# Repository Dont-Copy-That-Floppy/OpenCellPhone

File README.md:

# OpenCellPhone

**An open hardware + software cell phone using the global GSM network.**

Arduino-based and fully open-source, OpenCellPhone is a DIY mobile phone project that runs on AT commands, handles SMS/calls, and supports a touch-based interface with a custom-built GUI.

[2014/15 Hackaday Quarterfinalist](https://hackaday.io/project/2478-open-source-cell-phone)

---

## 🚀 Features

- Full support for **SMS send/receive**
- **Touch-based dial pad** and passcode lock screen
- **Call handling** (dial, receive, hang up)
- Basic **notifications**, **call timer**, and **incoming caller display**
- Real-time **clock display** from GSM module (`AT+CCLK`)
- Visual **signal strength** display (`AT+CSQ`)
- **Low-power display handling** with timeout/dim/sleep modes

---

## 🧠 Planned and Future Features

### Needed Features

- Lookup table for pixel width for screen formatting
- Sent SMS display and storage
- Secondary storage for messages
- Emergency calling from passcode screen
- In-call volume adjustment
- Call waiting support (`AT+CHLD`)
- Missed call tracking
- SMS management (delete, reorder, store)
- Signal strength meter
- Re-dial last number (`ATDL`)
- Notification screen with better intelligence

### Future Features

- Bluetooth & FM Radio
- Contact List / Phone Book
- Adjustable screen brightness
- Airplane mode (`AT+CFUN`)
- SMS sorting by sender/contact
- Swipe gestures for UI
- MMS view/send, image handling
- Light sensor and auto-brightness
- MP3/audio playback
- GPS & accelerometer
- Display output
- Web browser
- Ringtones
- Configurable settings via touch UI

---

## 📋 SIM Limitations

- SIM card storage is limited to **30 SMS messages**

---

## ⚙️ Build Info

### Architecture

- Built with **Arduino IDE**
- Written in C/C++ with **low-level serial AT command** integration
- GUI rendered using **RA8875 touchscreen driver**
- Touchscreen and backlight managed through **PWM and pin control**

### Libraries & Tools

- `RA8875` display/touch driver
- Standard `Serial`, `Wire`, and `SPI` Arduino libs
- Custom utility functions for character buffering and cursor logic

---

## 🧪 AT Command References

| Command                                   | Description                |
|-------------------------------------------|----------------------------|
| `ATD*99#`                                 | Dial Access Point          |
| `AT+CGDCONT=1,"IP","access.point.name"`   | Defines PDP context        |
| `AT+VRX`                                  | Record in-call audio       |
| `AT+COPS=?`                               | List available networks     |
| `AT+CSQ`                                  | Check signal strength      |
| `ATDL`                                    | Redial last number         |
| `AT+CHLD`                                 | Call waiting options       |

---

## 🧰 Development Setup

### Folder Structure

```text
/PrototypePhone
│
├── /lib                # Optional custom libraries
├── PrototypePhone.ino  # main file

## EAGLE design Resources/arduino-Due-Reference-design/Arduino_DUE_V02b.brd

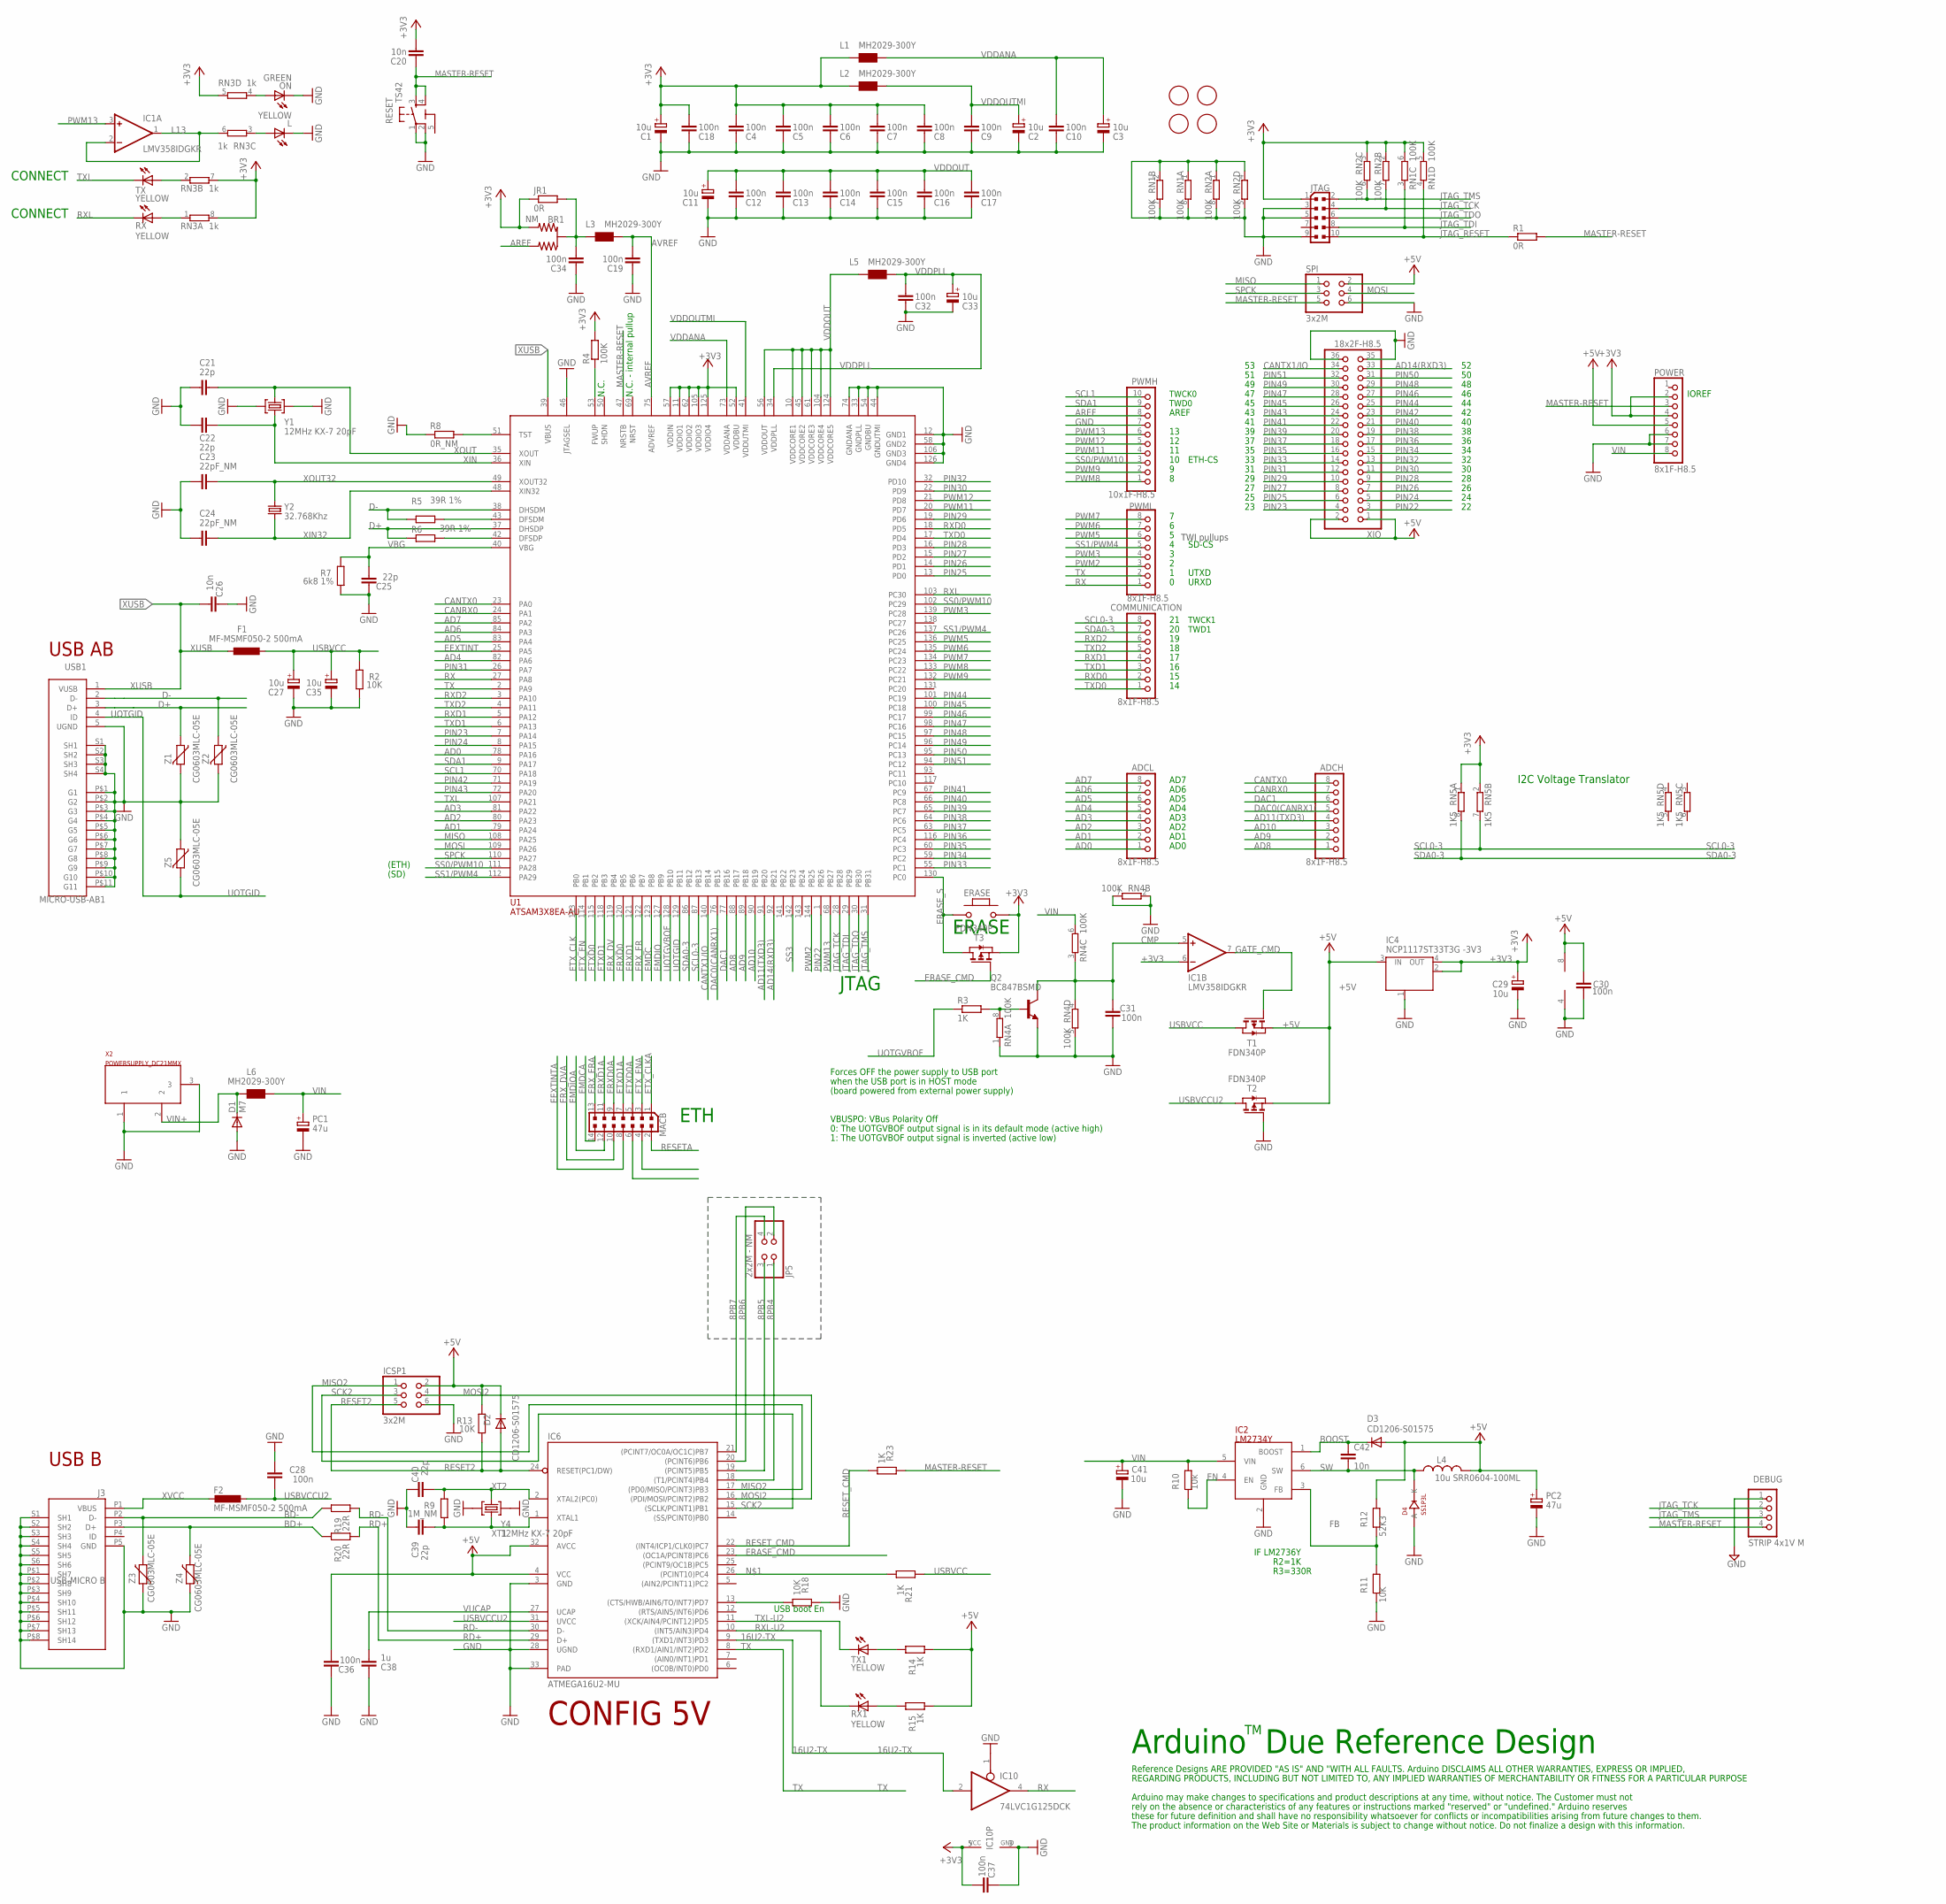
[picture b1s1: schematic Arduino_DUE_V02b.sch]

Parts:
ADCH: 8x1F-H8.5; 1X08
ADCL: 8x1F-H8.5; 1X08
BR1: NM; J0402
C1, C2, C3, C11, C27, C29, C33, C35, C41: 10u; SMC_B
C4, C5, C6, C7, C8, C9, C10, C12, C13, C14, C15, C16, C17, C18, C19, C28, C30, C31, C32, C34, C36, C37: 100n; C0402
C20, C26: 10n; C0402
C21, C22, C25, C39, C40: 22p; C0402
C23, C24: 22pF_NM; C0402
C38: 1u; C0402
C42: 10n; C0603-ROUND
COMMUNICATION: 8x1F-H8.5; 1X08
D1: M7; SMB
D2, D3: CD1206-S01575; MINIMELF
D4: SS1P3L; DO220AAL
DEBUG: STRIP 4x1V M; 1X04
ERASE: MYSMD_PB157; SMD_157SW
F1, F2: MF-MSMF050-2 500mA; L1812
FID1, FID2, FID3, FID4: FIDUCIALMOUNT; FIDUCIA-MOUNT
IC1: LMV358IDGKR; MSOP08
IC2: LM2734Y; SOT23-6
IC4: NCP1117ST33T3G -3V3; SOT223
IC6: ATMEGA16U2-MU; MLF32
IC10: 74LVC1G125DCK; SC70-5
ICSP1: 3x2M; 2X03
J3: USB-MICRO B; CON2_USB_MICRO_B_AT
JP5: 2x2M - NM; 2X02
JR1: 0R; R0402
JTAG: PINHEAD_PINHD-2X5PASSO127; PINHEAD_2X05_127
L: YELLOW; CHIP-LED0805
L1, L2, L3, L5, L6: MH2029-300Y; 0805
L4: 10u SRR0604-100ML; SRR0604
MACB: PINHEAD_PINHD-2X7PASSO127; PINHEAD_2X07_127
ON: GREEN; CHIP-LED0805
PC1, PC2: 47u; PANASONIC_D
POWER: 8x1F-H8.5; 1X08
PWMH: 10x1F-H8.5; 1X10
PWML: 8x1F-H8.5; 1X08
Q2: BC847BSMD; SOT23
R1: 0R; R0402
R2, R13, R18: 10K; R0402
R3, R14, R15, R21, R23: 1K; R0402
R4: 100K; R0402
R5, R6: 39R 1%; R0402
R7: 6k8 1%; R0603-ROUND
R8: 0R_NM; R0402
R9: 1M_NM; R0402
R10: 10k; R0402
R11: 10K; R0603-ROUND
R12: 52K3; R0603-ROUND
R19, R20: 22R; R0402
RESET: TS42
RN1, RN2, RN4: 100K; CAT16
RN3: 1k; CAY16
RN5: 1K5; CAT16
RX, RX1: YELLOW; CHIP-LED0805
SPI: 3x2M; 2X03
T1, T2, T3: FDN340P; SOT-23
TX, TX1: YELLOW; CHIP-LED0805
U1: ATSAM3X8EA-AU; LQFP144
USB1: MICRO-USB-AB1; MCR-AB1-S-RA-SMT
X2: POWERSUPPLY_DC21MMX; POWERSUPPLY_DC-21MM
XIO: 18x2F-H8.5; 2X18
Y1, Y4: 12MHz KX-7 20pF; CRYSTAL-3.2-2.5
Y2: 32.768Khz; RESONATOR_EPSON_FC_145
Z1, Z2, Z3, Z4, Z5: CG0603MLC-05E; CT/CN0603

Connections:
5-GND: RESET.5 (5-GND)
8PB4: IC6.18 ((T1/PCINT4)PB4), JP5.1
8PB5: IC6.19 ((PCINT5)PB5), JP5.3
8PB6: IC6.20 ((PCINT6)PB6), JP5.2
8PB7: IC6.21 ((PCINT7/OC0A/OC1C)PB7), JP5.4
16U2-TX: IC6.9 ((TXD1/INT3)PD3), IC10.2 (I)
+3V3: BR1.3 (2), C1.+, C4.2, C5.2, C6.2, C7.2, C8.2, C18.2, C20.2, C29.+, C37.1, ERASE.1, IC1.6 (-IN), IC4.2 (OUT), IC4.4 (OUT), IC10.5 (VCC), JR1.1, JTAG.1, L1.1, L2.1, POWER.2, POWER.4, R4.2, RN1.5 (2), RN1.6 (2), RN2.2 (1), RN2.3 (1), RN3.5 (2), RN3.7 (2), RN3.8 (2), RN5.1, RN5.2 (1), T3.2 (S), U1.11 (VDDIO1), U1.52 (VDDBU), U1.57 (VDDIN), U1.62 (VDDIO2), U1.105 (VDDIO3), U1.125 (VDDIO4)
+5V: C30.2, C36.1, D2.C, D3.A, IC1.8 (V+), IC4.3 (IN), IC6.4 (VCC), IC6.32 (AVCC), ICSP1.2, L4.P$2 (2), PC2.+, POWER.5, R12.1, R13.2, R14.1, R15.1, SPI.2, T1.2 (S), T2.2 (S), XIO.1, XIO.2
AD0: ADCL.1, U1.78 (PA16)
AD1: ADCL.2, U1.79 (PA24)
AD2: ADCL.3, U1.80 (PA23)
AD3: ADCL.4, U1.81 (PA22)
AD4: ADCL.5, U1.82 (PA6)
AD5: ADCL.6, U1.83 (PA4)
AD6: ADCL.7, U1.84 (PA3)
AD7: ADCL.8, U1.85 (PA2)
AD8: ADCH.1, U1.88 (PB17)
AD9: ADCH.2, U1.89 (PB18)
AD10: ADCH.3, U1.90 (PB19)
AD11(TXD3): ADCH.4, U1.91 (PB20)
AD14(RXD3): U1.92 (PB21), XIO.33
AREF: BR1.1, PWMH.8
AVREF: C19.2, L3.2, U1.75 (ADVREF)
AVREFL: BR1.2 (C), C34.2, JR1.2, L3.1
BD+: J3.P3 (D+), R20.2, Z4.2
BD-: J3.P2 (D-), R19.2, Z3.2
BOOST: C42.1, D3.C, IC2.1 (BOOST)
CANRX0: ADCH.7, U1.24 (PA1)
CANTX0: ADCH.8, U1.23 (PA0)
CANTX1/IO: U1.140 (PB14), XIO.34
CMP: C31.2, IC1.5 (+IN), Q2.3 (C), RN4.3 (1), RN4.4 (1)
D+: R6.1, U1.37 (DHSDP), USB1.3 (D+), Z1.1
D-: R5.1, U1.38 (DHSDM), USB1.2 (D-), Z2.1
DAC0(CANRX1): ADCH.5, U1.76 (PB15)
DAC1: ADCH.6, U1.77 (PB16)
DTR: IC6.13 ((CTS/HWB/AIN6/TO/INT7)PD7), R18.1
EEXTINT: U1.25 (PA5)
EEXTINTA: MACB.8
EMDC: U1.123 (PB8)
EMDCA: MACB.14
EMDIO: U1.127 (PB9)
EMDIOA: MACB.12 (13)
EN: IC2.4 (EN), R10.2
ERASE_CMD: IC6.23 ((OC1A/PCINT8)PC6), T3.3 (G)
ERASE_S: ERASE.2, T3.1 (D), U1.130 (PC0)
ERXD0: U1.120 (PB5)
ERXD0A: MACB.9
ERXD1: U1.121 (PB6)
ERXD1A: MACB.11
ERX_DV: U1.119 (PB4)
ERX_DVA: MACB.10
ERX_ER: U1.122 (PB7)
ERX_ERA: MACB.13 (12)
ETXD0: U1.115 (PB2)
ETXD0A: MACB.5
ETXD1: U1.118 (PB3)
ETXD1A: MACB.7
ETX_CLK: U1.113 (PB0)
ETX_CLKA: MACB.1
ETX_EN: U1.114 (PB1)
ETX_ENA: MACB.3
FB: IC2.3 (FB), R11.1, R12.2
GATE_CMD: IC1.7 (OUT), T1.3 (G)
GND: C1.-, C2.-, C3.-, C4.1, C5.1, C6.1, C7.1, C8.1, C9.1, C10.1, C11.-, C12.1, C13.1, C14.1, C15.1, C16.1, C17.1, C18.1, C19.1, C21.2, C22.2, C23.2, C24.2, C25.2, C26.2, C27.-, C28.2, C29.-, C30.1, C31.1, C32.1, C33.-, C34.1, C35.-, C36.2, C37.2, C38.2, C39.2, C40.2, C41.-, D1.A, D4.P$2 (A), DEBUG.1, IC1.4 (V-), IC2.2 (GND), IC4.1 (GND/ADJ), IC6.3 (GND), IC6.28 (UGND), IC6.33 (PAD), IC10.1 (OE), IC10.3 (GND), ICSP1.6, J3.P5 (GND), J3.P$1 (SH7), J3.P$2 (SH8), J3.P$3 (SH9), J3.P$4 (SH10), J3.P$5 (SH11), J3.P$6 (SH12), J3.P$7 (SH13), J3.P$8 (SH14), J3.S1 (SH1), J3.S2 (SH2), J3.S3 (SH3), J3.S4 (SH4), J3.S5 (SH5), J3.S6 (SH6), JTAG.3, JTAG.5, JTAG.9, L.C, ON.C, PC1.-, PC2.-, POWER.6, POWER.7, PWMH.7, Q2.2 (E), R2.1, R7.1, R8.1, R11.2, R18.2, RESET.1, RESET.2, RN1.1, RN1.2 (1), RN1.7 (2), RN1.8 (2), RN2.1, RN2.4 (1), RN2.5 (2), RN2.8 (2), RN4.1, RN4.2 (1), RN4.5 (2), RN4.7 (2), SPI.6, T2.3 (G), U1.12 (GND1), U1.33 (GNDPLL), U1.44 (GNDUTMI), U1.46 (JTAGSEL), U1.54 (GNDBU), U1.58 (GND2), U1.74 (GNDANA), U1.106 (GND3), U1.126 (GND4), USB1.5 (UGND), USB1.P$1 (G1), USB1.P$2 (G2), USB1.P$3 (G3), USB1.P$4 (G4), USB1.P$5 (G5), USB1.P$6 (G6), USB1.P$7 (G7), USB1.P$8 (G8), USB1.P$9 (G9), USB1.P$10 (G10), USB1.P$11 (G11), USB1.S1 (SH1), USB1.S2 (SH2), USB1.S3 (SH3), USB1.S4 (SH4), X2.1, X2.3, XIO.35, XIO.36, Y1.2 (GND), Y1.4 (GND), Y4.2 (GND), Y4.4 (GND), Z1.2, Z2.2, Z3.1, Z4.1, Z5.1
JTAG_RESET: JTAG.10, R1.1, RN1.4 (1)
JTAG_TCK: DEBUG.2, JTAG.4, RN2.7 (2), U1.28 (PB28)
JTAG_TDI: JTAG.8, RN1.3 (1), U1.29 (PB29)
JTAG_TDO: JTAG.6, U1.30 (PB30)
JTAG_TMS: DEBUG.3, JTAG.2, RN2.6 (2), U1.31 (PB31)
L13: IC1.1 (OUT), IC1.2 (-IN), RN3.6 (2)
MASTER-RESET: C20.1, DEBUG.4, POWER.3, R1.2, R23.2, RESET.3, RESET.4, SPI.5, U1.47 (NRSTB)
MISO: SPI.1, U1.108 (PA25)
MISO2: IC6.17 ((PD0/MISO/PCINT3)PB3), ICSP1.1
MOSI: SPI.4, U1.109 (PA26)
MOSI2: IC6.16 ((PDI/MOSI/PCINT2)PB2), ICSP1.4
unnamed: IC6.26 ((PCINT10)PC4), R21.1
unnamed: L.A, RN3.3 (1)
unnamed: ON.A, RN3.4 (1)
unnamed: R15.2, RX1.A
unnamed: R8.2, U1.51 (TST)
unnamed: Q2.1 (B), R3.2, RN4.8 (2)
unnamed: R4.1, U1.53 (FWUP)
unnamed: R5.2, U1.43 (DFSDM)
unnamed: R6.2, U1.42 (DFSDP)
unnamed: R14.2, TX1.A
unnamed: RN3.1, RX.A
unnamed: RN3.2 (1), TX.A
PIN22: U1.1 (PB26), XIO.3
PIN23: U1.7 (PA14), XIO.4
PIN24: U1.8 (PA15), XIO.5
PIN25: U1.13 (PD0), XIO.6
PIN26: U1.14 (PD1), XIO.7
PIN27: U1.15 (PD2), XIO.8
PIN28: U1.16 (PD3), XIO.9
PIN29: U1.19 (PD6), XIO.10
PIN30: U1.22 (PD9), XIO.11
PIN31: U1.26 (PA7), XIO.12
PIN32: U1.32 (PD10), XIO.13
PIN33: U1.55 (PC1), XIO.14
PIN34: U1.59 (PC2), XIO.15
PIN35: U1.60 (PC3), XIO.16
PIN36: U1.116 (PC4), XIO.17
PIN37: U1.63 (PC5), XIO.18
PIN38: U1.64 (PC6), XIO.19
PIN39: U1.65 (PC7), XIO.20
PIN40: U1.66 (PC8), XIO.21
PIN41: U1.67 (PC9), XIO.22
PIN42: U1.71 (PA19), XIO.23
PIN43: U1.72 (PA20), XIO.24
PIN44: U1.101 (PC19), XIO.25
PIN45: U1.100 (PC18), XIO.26
PIN46: U1.99 (PC17), XIO.27
PIN47: U1.98 (PC16), XIO.28
PIN48: U1.97 (PC15), XIO.29
PIN49: U1.96 (PC14), XIO.30
PIN50: U1.95 (PC13), XIO.31
PIN51: U1.94 (PC12), XIO.32
PWM2: PWML.3, U1.144 (PB25)
PWM3: PWML.4, U1.139 (PC28)
PWM5: PWML.6, U1.136 (PC25)
PWM6: PWML.7, U1.135 (PC24)
PWM7: PWML.8, U1.134 (PC23)
PWM8: PWMH.1, U1.133 (PC22)
PWM9: PWMH.2, U1.132 (PC21)
PWM11: PWMH.4, U1.20 (PD7)
PWM12: PWMH.5, U1.21 (PD8)
PWM13: IC1.3 (+IN), PWMH.6, U1.68 (PB27)
RD+: IC6.29 (D+), R20.1
RD-: IC6.30 (D-), R19.1
RESET2: D2.A, IC6.24 (RESET(PC1/DW)), ICSP1.5, R13.1
RESETA: MACB.2
RESET_CMD: IC6.22 ((INT4/ICP1/CLK0)PC7), R23.1
RX: IC10.4 (O), PWML.1, U1.27 (PA8)
RXD0: COMMUNICATION.2, U1.18 (PD5)
RXD1: COMMUNICATION.4, U1.5 (PA12)
RXD2: COMMUNICATION.6, U1.3 (PA10)
RXL: RX.C, U1.103 (PC30)
RXL-U2: IC6.10 ((INT5/AIN3)PD4), RX1.C
SCK2: IC6.15 ((SCLK/PCINT1)PB1), ICSP1.3
SCL0-3: COMMUNICATION.8, RN5.7 (2), U1.87 (PB13)
SCL1: PWMH.10, U1.70 (PA18)
SDA0-3: COMMUNICATION.7, RN5.8 (2), U1.86 (PB12)
SDA1: PWMH.9, U1.9 (PA17)
SPCK: SPI.3, U1.110 (PA27)
SS0/PWM10: PWMH.3, U1.102 (PC29), U1.111 (PA28)
SS1/PWM4: PWML.5, U1.112 (PA29), U1.137 (PC26)
SS3: U1.142 (PB23)
SW: C42.2, D4.P$1 (K), IC2.6 (SW), L4.P$1 (1)
TX: IC6.8 ((RXD1/AIN1/INT2)PD2), PWML.2, U1.2 (PA9)
TXD0: COMMUNICATION.1, U1.17 (PD4)
TXD1: COMMUNICATION.3, U1.6 (PA13)
TXD2: COMMUNICATION.5, U1.4 (PA11)
TXL: TX.C, U1.107 (PA21)
TXL-U2: IC6.11 ((XCK/AIN4/PCINT12)PD5), TX1.C
UOTGID: U1.129 (PB11), USB1.4 (ID), Z5.2
UOTGVBOF: R3.1, U1.128 (PB10)
USBVCC: C27.+, C35.+, F1.1, R2.2, R21.2, T1.1 (D)
USBVCCU2: C28.1, F2.1, IC6.31 (UVCC), T2.1 (D)
VBG: C25.1, R7.2, U1.40 (VBG)
VDDANA: C3.+, C10.2, L1.2, U1.73 (VDDANA)
VDDOUT: C11.+, C12.2, C13.2, C14.2, C15.2, C16.2, C17.2, L5.1, U1.10 (VDDCORE1), U1.45 (VDDCORE2), U1.56 (VDDOUT), U1.61 (VDDCORE3), U1.104 (VDDCORE4), U1.124 (VDDCORE5)
VDDOUTMI: C2.+, C9.2, L2.2, U1.41 (VDDUTMI)
VDDPLL: C32.2, C33.+, L5.2, U1.34 (VDDPLL)
VIN: C41.+, IC2.5 (VIN), L6.1, PC1.+, POWER.8, R10.1, RN4.6 (2)
VIN+: D1.C, L6.2, X2.2
VUCAP: C38.1, IC6.27 (UCAP)
XIN: C22.1, U1.36 (XIN), Y1.1 (C1)
XIN32: C24.1, U1.48 (XIN32), Y2.P$2 (2)
XOUT: C21.1, U1.35 (XOUT), Y1.3 (C2)
XOUT32: C23.1, U1.49 (XOUT32), Y2.P$1 (1)
XT1: C39.1, IC6.1 (XTAL1), R9.1, Y4.1 (C1)
XT2: C40.1, IC6.2 (XTAL2(PC0)), R9.2, Y4.3 (C2)
XUSB: C26.1, F1.2, U1.39 (VBUS), USB1.1 (VUSB)
XVCC: F2.2, J3.P1 (VBUS)

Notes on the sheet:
TWI pullups
TWCK1
TWD1
IOREF
TWCK0
TWD0
AD1
AD2
AD3
AD4
AD5
AD6
AD0
USB AB
AREF
AD7
SD-CS
Forces OFF the power supply to USB port
when the USB port is in HOST mode
(board powered from external power supply)
N.C.
JTAG
ERASE
CONNECT
VBUSPO: VBus Polarity Off
0: The UOTGVBOF output signal is in its default mode (active high)
1: The UOTGVBOF output signal is inverted (active low)
ETH
UTXD
URXD
(ETH)
(SD)
ETH-CS
I2C Voltage Translator
USB boot En
IF LM2736Y
R2=1K
R3=330R
CONFIG 5V
USB B

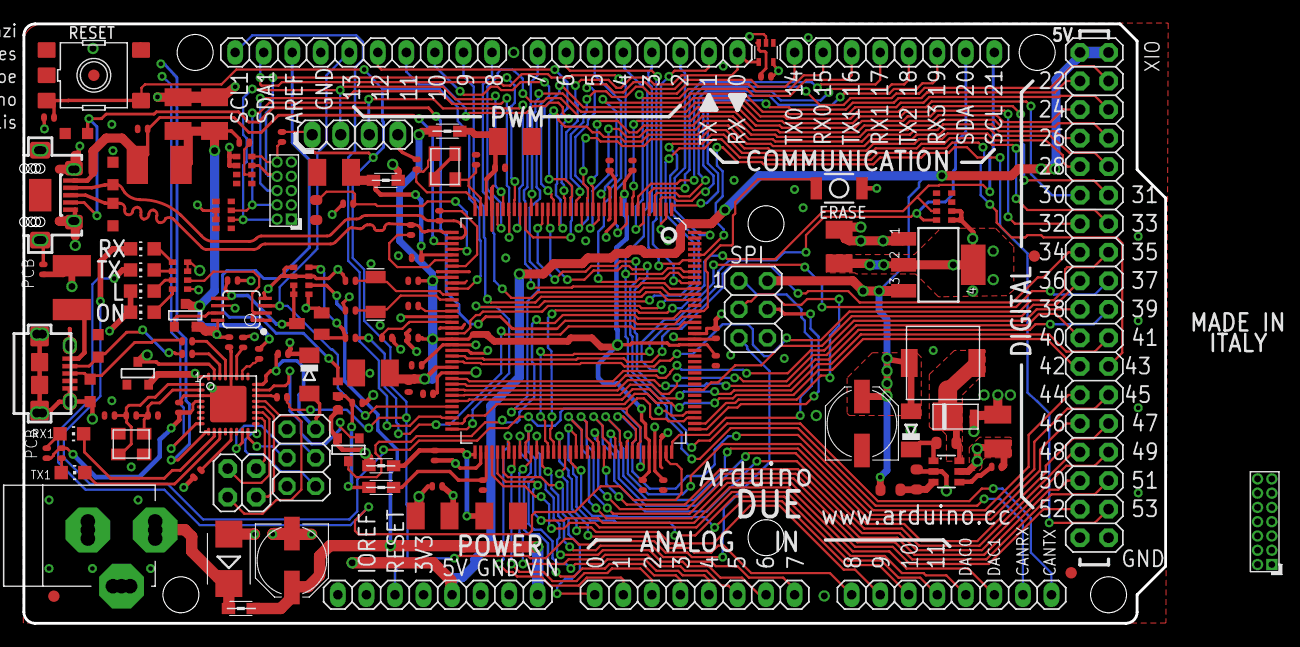
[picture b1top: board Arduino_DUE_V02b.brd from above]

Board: 4 copper layers, 101.6 x 53.3 mm, 130 parts (0 on the bottom side), 149 nets.

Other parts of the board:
E$1: DISC

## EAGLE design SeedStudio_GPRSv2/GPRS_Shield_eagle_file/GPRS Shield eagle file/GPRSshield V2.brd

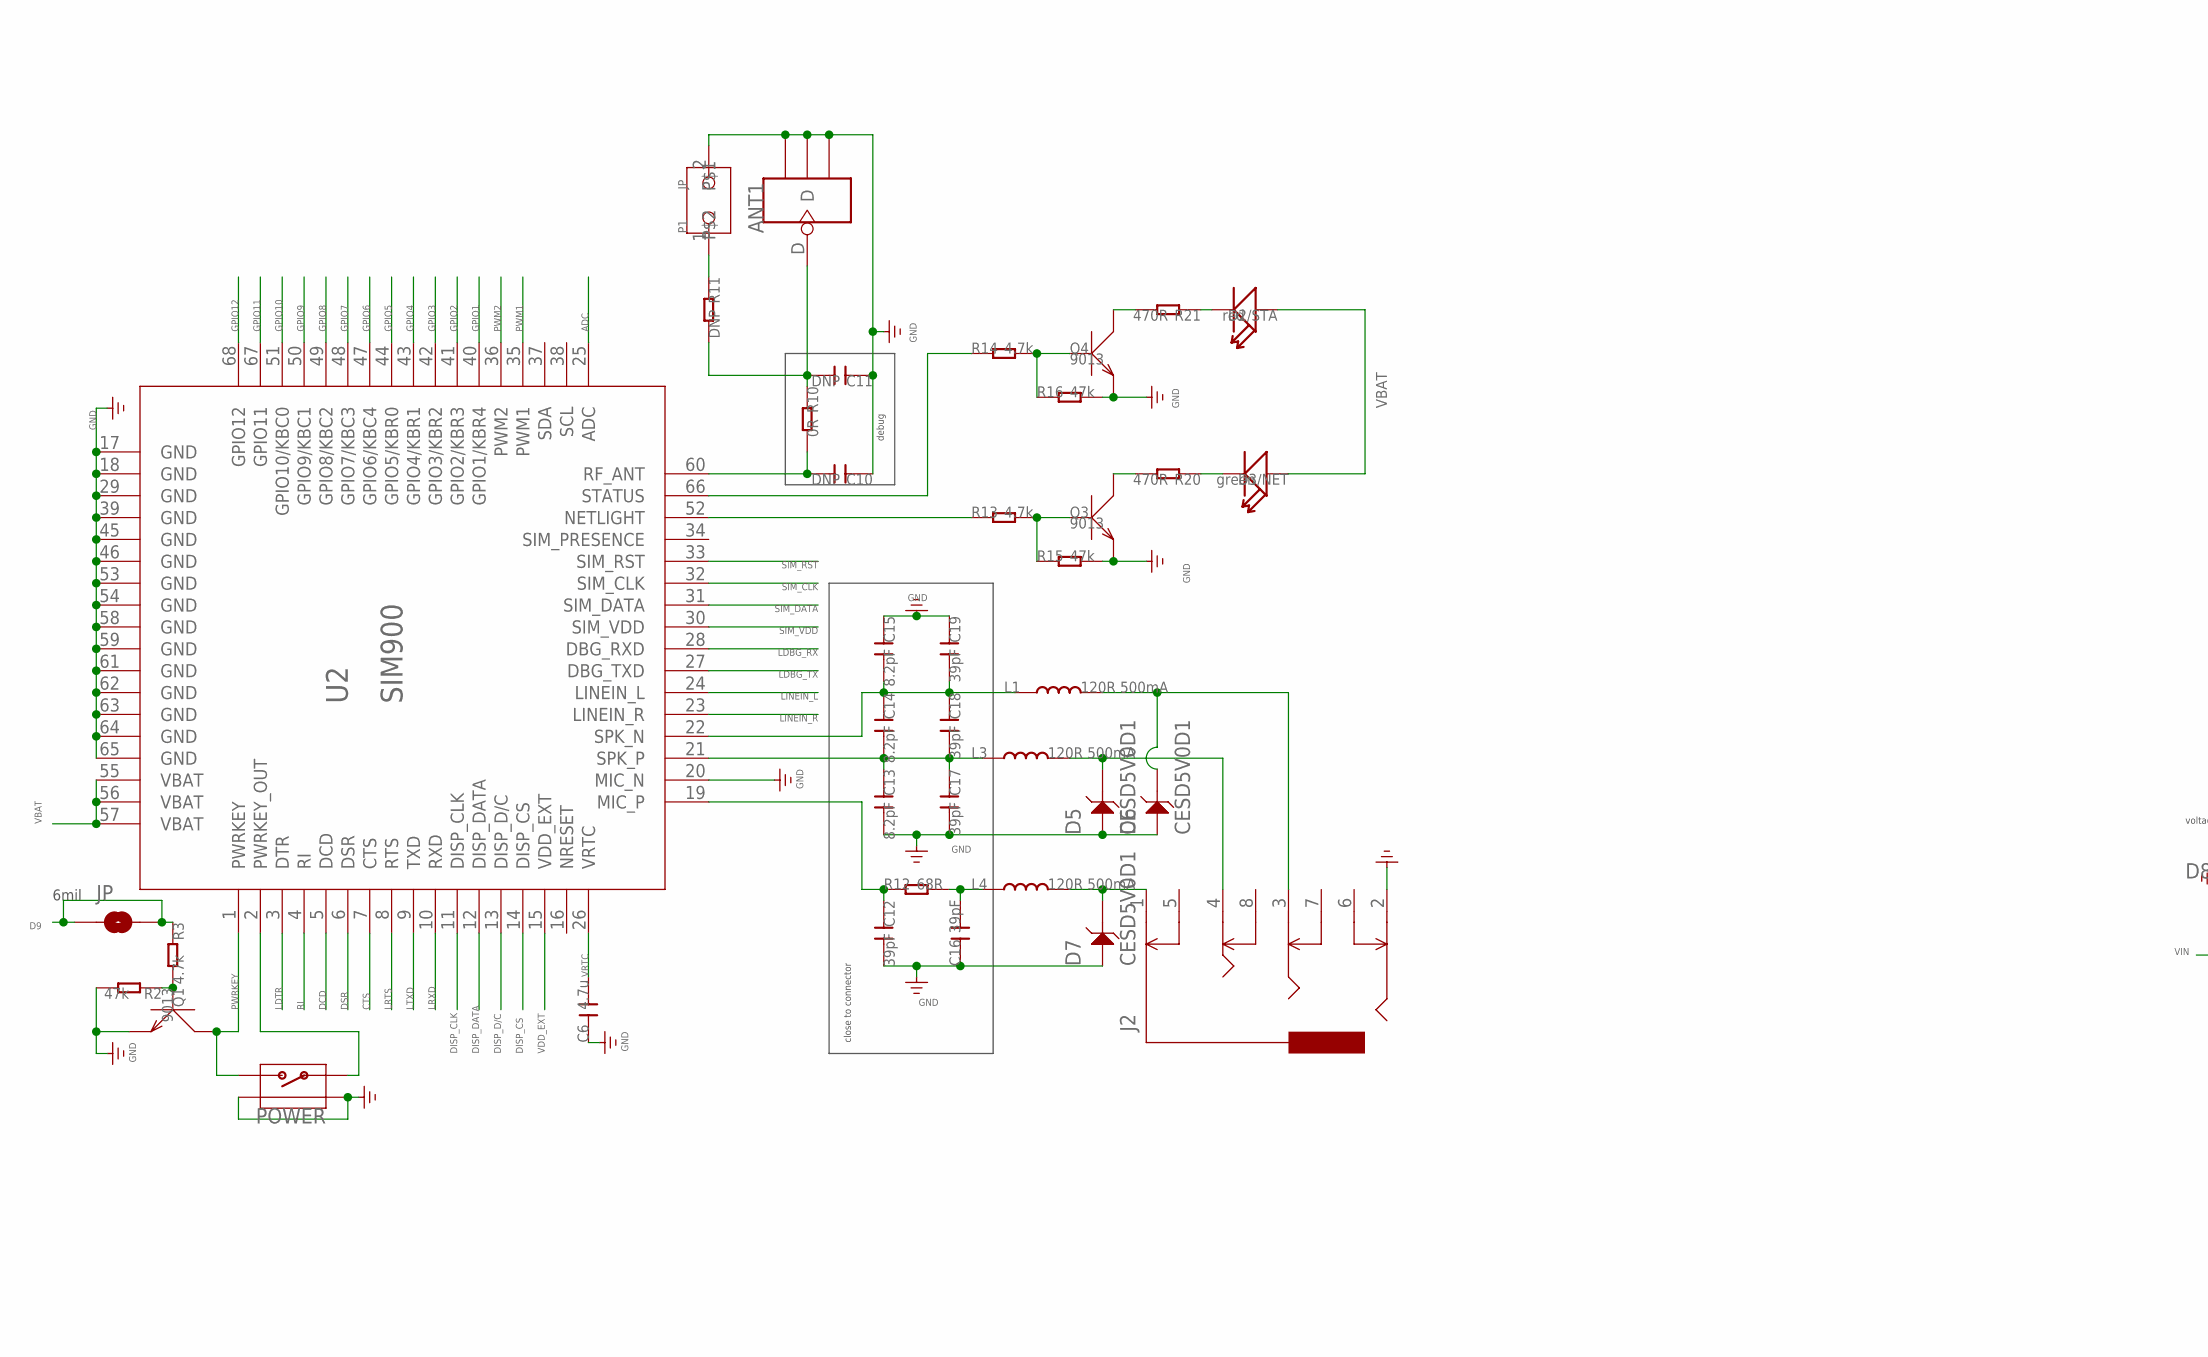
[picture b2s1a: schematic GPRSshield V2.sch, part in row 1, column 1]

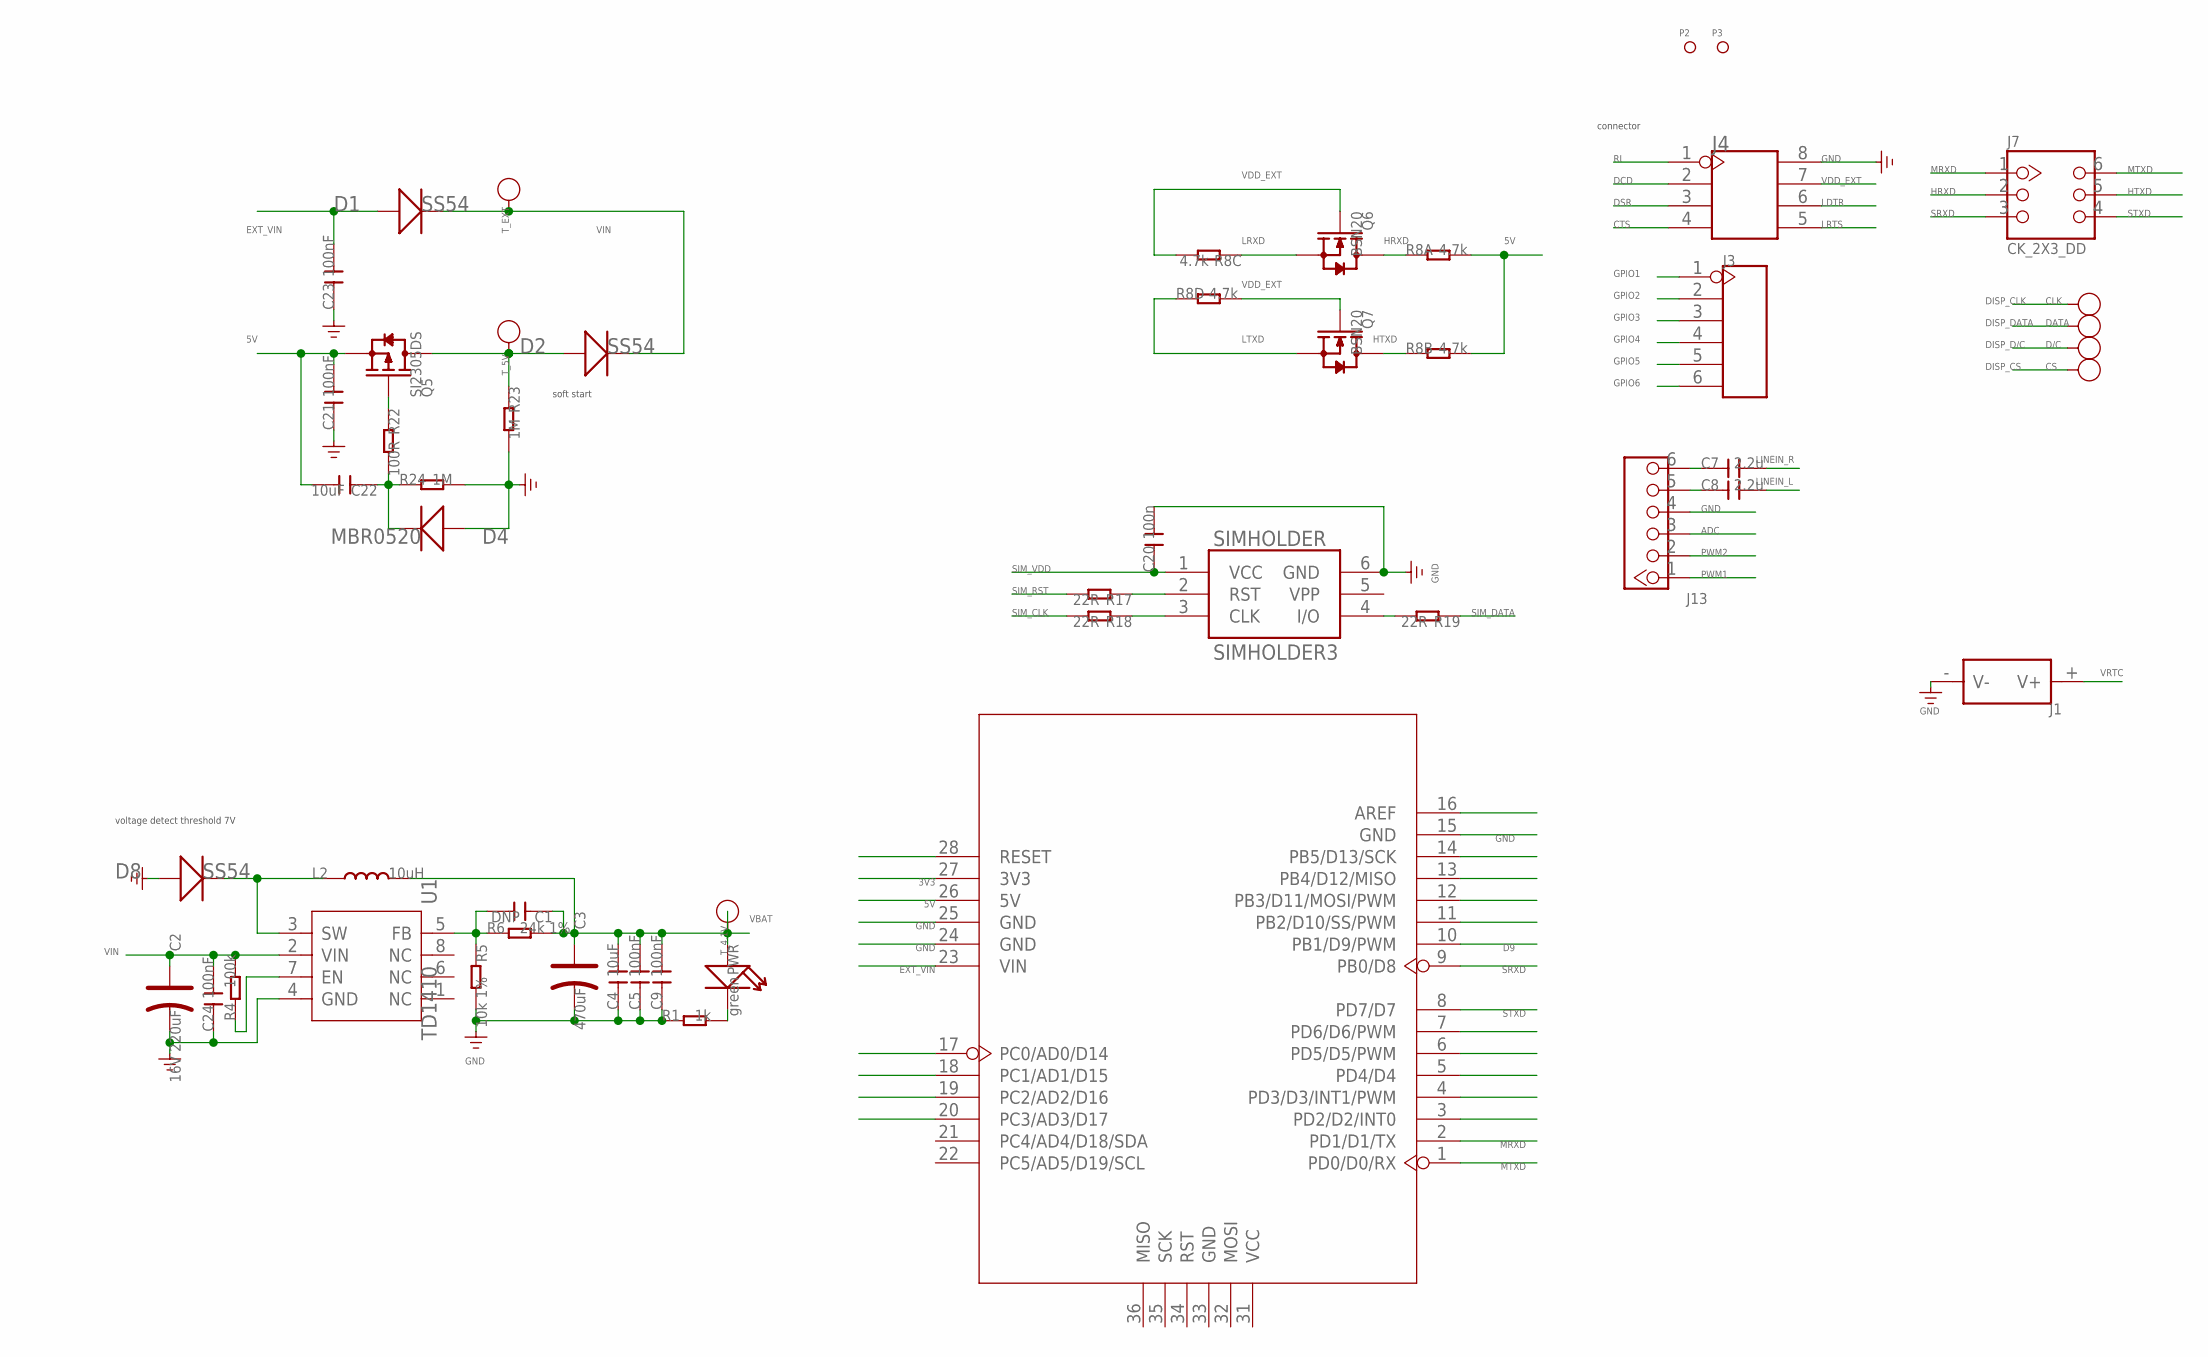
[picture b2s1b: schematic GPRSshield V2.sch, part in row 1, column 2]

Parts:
ANT1: ANTENNA-U-FL; 4P-U-FL
C1, C10, C11: DNP; C0603
C2: 16V 220uF; ELECTRO-SMD-D-5.6MM
C3: 470uF; AVX-D
C4, C22: 10uF; C0805
C5, C9, C21, C23, C24: 100nF; C0603
C6: 4.7u; C0805
C7, C8: 2.2u; C0805
C12, C16, C17, C18, C19: 39pF; C0603
C13, C14, C15: 8.2pF; C0603
C20: 100n; C0603
CLK: PAD-TEST-POINT-CIRCLE'4545'; TP_4545
CS: PAD-TEST-POINT-CIRCLE'4545'; TP_4545
D1, D2, D8: SS54; SMB
D2/STA: red; LED-0603
D3/NET: green; LED-0603
D4: MBR0520; SOD123-2.7X1.6
D5, D6, D7: CESD5V0D1; SOD123-2.7X1.6
D/C: PAD-TEST-POINT-CIRCLE'4545'; TP_4545
DATA: PAD-TEST-POINT-CIRCLE'4545'; TP_4545
J1: HOLDER-BAT; SMD-CR1220-2
J2: AUDIO-8P'PJ-3536-L6S'; 8P-3.5-SMD
J3: HEADER-6P-65/35MIL; 6P-2.54-65/35MIL
J4: HEADER-2X4P-2.54; 2X4P-2.54
J7: CK_2X3_DD; CK_2X3
J13: HEADER_1X6; CK_1X6
JP: PAD-SOLDERJUMPERNC; 2P-SMD-3.3X2
L1, L3, L4: 120R 500mA; L0603
L2: 10uH; L0630
P1: JP
P2, P3: PAD-MARK; ROUND-MARK-1.0
POWER: BUTTON-4P-REINFORCE'TS-118E'; 4P-SMD-7X3.5X3.5H
PWR: green; D0603
Q1, Q3, Q4: 9013; SOT23
Q5: SI2305DS; SOT23
Q6, Q7: BSN20; SOT23
R1: 1k; R0603
R2, R15, R16: 47k; R0603
R3, R13, R14: 4.7k; R0603
R4: 100k; R0603
R5: 10k 1%; R0603
R6: 24k 1%; R0603
R8: 4.7k; 1206-8-3.3X2.4
R10: 0R; R0603
R11: DNP; R0603
R12: 68R; R0603
R17, R18, R19: 22R; R0603
R20, R21: 470R; R0603
R22: 100R; R0603
R23, R24: 1M; R0603
SIMHOLDER: SIMHOLDER3
T_4.1V, T_5V: PAD-TEST-POINT-CIRCLE'4545'; TP_4545; PARTNO DNP
T_EXT: PAD-TEST-POINT-CIRCLE'4545'; TP_4545; PARTNO DNP
U1: TD1410; SOP8
U2: SIM900
U3: ARDUINO'W/O-SILK'; ARDUINO-W/O-SILK

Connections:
3V3: U3.27 (3V3)
5V: C21.2, C22.2, Q5.2 (S), R8.7 (2), R8.8 (2), U3.26 (5V)
ADC: J13.3, U2.25 (ADC)
CTS: J4.4, U2.7 (CTS)
D9: JP.1, JP.2, R3.1, U3.10 (PB1/D9/PWM)
DCD: J4.2, U2.5 (DCD)
DISP_CLK: CLK.T, U2.11 (DISP_CLK)
DISP_CS: CS.T, U2.14 (DISP_CS)
DISP_D/C: D/C.T, U2.13 (DISP_D/C)
DISP_DATA: DATA.T, U2.12 (DISP_DATA)
DSR: J4.3, U2.6 (DSR)
EXT_VIN: C23.2, D1.+, U3.23 (VIN)
GND: ANT1.GND1, ANT1.GND2, ANT1.GND3, C2.-, C3.-, C4.1, C5.1, C6.1, C9.1, C10.1, C11.1, C12.2, C13.2, C15.1, C16.1, C17.2, C19.1, C20.2, C21.1, C23.1, C24.1, D4.1 (+), D5.1, D6.1, D7.1, D8.+, J1.- (V-), J2.2, J4.8, J13.4, P1.2, POWER.S1, POWER.S2, Q1.2 (E), Q3.2 (E), Q4.2 (E), R1.1, R2.2, R5.2, R15.2, R16.2, R23.2, R24.2, SIMHOLDER.6 (GND), U1.4 (GND), U2.17 (GND), U2.18 (GND), U2.20 (MIC_N), U2.29 (GND), U2.39 (GND), U2.45 (GND), U2.46 (GND), U2.53 (GND), U2.54 (GND), U2.58 (GND), U2.59 (GND), U2.61 (GND), U2.62 (GND), U2.63 (GND), U2.64 (GND), U2.65 (GND), U3.15 (GND), U3.24 (GND), U3.25 (GND)
GPIO1: J3.1, U2.40 (GPIO1/KBR4)
GPIO2: J3.2, U2.41 (GPIO2/KBR3)
GPIO3: J3.3, U2.42 (GPIO3/KBR2)
GPIO4: J3.4, U2.43 (GPIO4/KBR1)
GPIO5: J3.5, U2.44 (GPIO5/KBR0)
GPIO6: J3.6, U2.47 (GPIO6/KBC4)
GPIO7: U2.48 (GPIO7/KBC3)
GPIO8: U2.49 (GPIO8/KBC2)
GPIO9: U2.50 (GPIO9/KBC1)
GPIO10: U2.51 (GPIO10/KBC0)
GPIO11: U2.67 (GPIO11)
GPIO12: U2.68 (GPIO12)
HRXD: J7.2, Q6.3 (D), R8.1
HTXD: J7.5, Q7.3 (D), R8.2 (1)
LDBG_RX: U2.28 (DBG_RXD)
LDBG_TX: U2.27 (DBG_TXD)
LDTR: J4.6, U2.3 (DTR)
LINEIN_L: C8.2, U2.24 (LINEIN_L)
LINEIN_R: C7.2, U2.23 (LINEIN_R)
LRTS: J4.5, U2.8 (RTS)
LRXD: Q6.2 (S), R8.3 (1), U2.10 (RXD)
LTXD: Q7.2 (S), R8.4 (1), U2.9 (TXD)
MRXD: J7.1, U3.2 (PD1/D1/TX)
MTXD: J7.6, U3.1 (PD0/D0/RX)
unnamed: C10.2, R10.2, U2.60 (RF_ANT)
unnamed: D2.+, Q5.3 (D), R23.1, T_5V.T
unnamed: Q3.3 (C), R20.2
unnamed: R19.2, SIMHOLDER.4 (I/O)
unnamed: R18.1, SIMHOLDER.3 (CLK)
unnamed: R17.1, SIMHOLDER.2 (RST)
unnamed: D3/NET.-, R20.1
unnamed: Q3.1 (B), R13.2, R15.1
unnamed: PWR.-, R1.2
unnamed: R13.1, U2.52 (NETLIGHT)
unnamed: POWER.1, U2.2 (PWRKEY_OUT)
unnamed: R4.1, U1.7 (EN)
unnamed: C12.1, R12.1, U2.19 (MIC_P)
unnamed: C13.1, C14.2, C17.1, C18.2, L3.1, U2.21 (SPK_P)
unnamed: Q4.3 (C), R21.2
unnamed: D2/STA.-, R21.1
unnamed: Q4.1 (B), R14.2, R16.1
unnamed: C14.1, C15.2, C18.1, C19.2, L1.1, U2.22 (SPK_N)
unnamed: R14.1, U2.66 (STATUS)
unnamed: ANT1.D, C11.2, R10.1, R11.2
unnamed: C7.1, J13.6
unnamed: C8.1, J13.5
unnamed: C16.2, L4.1, R12.2
unnamed: Q5.1 (G), R22.1
unnamed: Q1.1 (B), R2.1, R3.2
unnamed: D8.-, L2.1, U1.3 (SW)
unnamed: C22.1, D4.2 (-), R22.2, R24.1
unnamed: D7.2, J2.1, L4.2
unnamed: C1.2, R5.1, R6.1, U1.5 (FB)
unnamed: D5.2, J2.4, L3.2
unnamed: D6.2, J2.3, L1.2
unnamed: P1.1, R11.1
PWM1: J13.1, U2.35 (PWM1)
PWM2: J13.2, U2.36 (PWM2)
PWRKEY: POWER.2, Q1.3 (C), U2.1 (PWRKEY)
RI: J4.1, U2.4 (RI)
SIM_CLK: R18.2, U2.32 (SIM_CLK)
SIM_DATA: R19.1, U2.31 (SIM_DATA)
SIM_RST: R17.2, U2.33 (SIM_RST)
SIM_VDD: C20.1, SIMHOLDER.1 (VCC), U2.30 (SIM_VDD)
SRXD: J7.3, U3.9 (PB0/D8)
STXD: J7.4, U3.8 (PD7/D7)
VBAT: C1.1, C3.+, C4.2, C5.2, C9.2, D2/STA.+, D3/NET.+, L2.2, PWR.+, R6.2, T_4.1V.T, U2.55 (VBAT), U2.56 (VBAT), U2.57 (VBAT)
VDD_EXT: J4.7, Q6.1 (G), Q7.1 (G), R8.5 (2), R8.6 (2), U2.15 (VDD_EXT)
VIN: C2.+, C24.2, D1.-, D2.-, R4.2, T_EXT.T, U1.2 (VIN)
VRTC: C6.2, J1.+ (V+), U2.26 (VRTC)

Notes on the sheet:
close to connector
debug
soft start
voltage detect threshold 7V
connector
6mil
